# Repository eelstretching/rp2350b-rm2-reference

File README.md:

# RP2350B + RM2

Raspberry Pi's RP2350B minimal design (RPI-RP2350B-MINIMAL R4-S1, KiCad 10) with these additions:

- the **RM2** Wi-Fi/Bluetooth module (CYW43439) on **GPIO 43-46**
- the **8 MB APS6404L PSRAM** fitted on the second QSPI chip select, moved from GPIO0 to **GPIO47**
- **single-row headers**: J2/J3 are 1x29 / 1x28 rows with the GPIOs in order and **3V3 and GND
  pins at both ends**, in place of Pi's 2x26 headers with an all-GND outer row. That makes the
  board easy to use on perfboard, with 3.3 V on hand for level shifters and the like
- a **5 V input (VSYS) on J3 pin 2**, so the board can run without USB. As on a Pico, USB comes in
  through a Schottky diode (D2), so 5 V on the header can't back-feed a computer's USB port

That leaves **GPIO 0-42 free and in order** on the J2/J3 headers, instead of the Pico 2 W's gap
at 23/24/25/29.

Status: **schematic and layout done, DRC clean, not yet fabricated.** See "Layout" for what changed
on Pi's board.

## Pin map

| GPIO | Use |
|---|---|
| 0-42 | free, on J2/J3 (0/1 = default UART0) |
| 43 | RM2 WL_ON + BT_ON |
| 44 | RM2 gSPI CS |
| 45 | RM2 gSPI DATA: DI direct, DO through 470R (R14), IRQ through 10k (R15) |
| 46 | RM2 gSPI CLK |
| 47 | PSRAM chip select (XIP_SS_N[1]), 10k pull-up R13, 0R link R11 |

GPIO 43-47 aren't on the headers: they belong to the radio and the PSRAM.

The headers, from the USB end down:

| Header | Top | Middle | Bottom |
|---|---|---|---|
| J2 (left, 29 pins) | 3V3 | GP0-GP24 | GND, 3V3, GND |
| J3 (right, 28 pins) | 3V3, VSYS, GND, GND, GND | GP42-GP28, RUN, SWD, SWCLK, GP27-GP25 | 3V3, GND |

The radio circuit is the Pico 2 W's (and the RM2 datasheet's) on different pins:

- VIN and VDDIO go to +3V3, with 10u + 2x 100n local decoupling.
- WL_GPIO0 drives a green LED (D1) through 1k. That's the SDK's `CYW43_WL_GPIO_LED_PIN`.
- WL_GPIO1, WL_GPIO2 and the NC pins aren't connected.

The cyw43 driver takes any pins from the board header, so nothing else changes in firmware. On the
RP2350B a PIO block reaches either GPIO 0-31 or 16-47. The radio's PIO therefore sits in the
16-47 window, which means LED output PIOs for GPIO 0-15 must use a different PIO block.

## Power

The board runs from USB, or from 5 V on **J3 pin 2 (VSYS)**, which works like a Pico's VSYS pin.

- VSYS feeds U2, the 3.3 V regulator (NCP1117, linear). USB's VBUS reaches VSYS through D2
  (B5819W Schottky). D2 blocks 5 V on the header from flowing back into a computer, so you can leave
  USB plugged in for flashing and serial while the header powers the board. With both connected,
  the header supply (no diode drop) carries the load.
- Give VSYS 4.75-5.5 V. U2 needs about 1.2 V of headroom, and anything above 3.3 V plus that
  headroom turns into heat in U2.
- **From a 12 V supply** (the lights' supply, say), step it down to 5 V with a small buck module
  and wire that to VSYS and GND. Don't put 12 V on VSYS directly: U2 would burn (12 - 3.3) V times
  the board's current, nearly 1 W at 100 mA, which is too much for a SOT-223 on this copper.
- On USB alone, D2 drops about 0.3-0.4 V, which leaves U2 enough headroom from a normal USB port.
- The 3V3 pins are U2's output. They're fine for level shifters and sensors (tens of mA). U2 also
  carries the RP2350 and the radio, and it turns (VSYS - 3.3 V) times the total current into heat.
- VSYS has no reverse-polarity protection, so check the polarity before powering up.

## Using it on perfboard

J2 and J3 are single rows on the 0.1" grid, 1.7" (17 holes) apart, so the module drops straight
into perfboard, and every pin has free holes beside it.

- **Socket it and wire on the underside.** Put female headers on the perfboard and plug the module
  in, then wire underneath with thin insulated wire (Kynar or wire-wrap). The area under the module
  is free routing space. Socketing also gives the parts on the module's underside room: U4 (the
  PSRAM, 1.75 mm tall SOIC), R11, R13 and C22. Plain header pins pushed fully home leave only
  about 2.5 mm.
- **Keep the antenna end clear.** Let the RM2 end overhang the perfboard edge, or keep that area
  free of wires, copper and ground. Anything conductive close under the antenna detunes it.

Two traps:

- **Stripboard (Veroboard):** run the strips outward, perpendicular to the headers, so each pin
  gets its own strip. Then cut every strip somewhere between the two headers. Otherwise a strip
  runs under the module and joins each J2 pin to the J3 pin in the same row: GPIO0 to 3V3,
  GPIO1 to GND, and at the bottom 3V3 straight to GND.
- **Solderless breadboard:** the 1.7" span between the rows is too wide to straddle a standard
  breadboard.

## PSRAM in your own code

With pico-sdk 2.3.0 or later, linking `hardware_psram` brings the PSRAM up at boot. It reads
`PICO_PSRAM_CS_PIN` and `PICO_PSRAM_SIZE_BYTES`, which the board header already sets. The PSRAM then
appears as ordinary memory at 0x11000000.

- **Static data:** `__uninitialized_psram("name")` (or `__in_psram("name")` for initialised data)
  places a variable or array in PSRAM.
- **Dynamic allocation:** `firmware/psram_alloc` adds `psram_malloc`, `psram_calloc`,
  `psram_realloc`, `psram_memalign` and `psram_free`, plus `psram_heap_stats()`. These work like
  malloc (8-byte aligned, safe from both cores, not from interrupt handlers) but allocate from the
  PSRAM left after any PSRAM variables. The SDK's own `malloc` stays in the faster on-chip SRAM.
  It's a TLSF allocator with its control block in SRAM. To use it:

  ```cmake
  add_subdirectory(path/to/firmware/psram_alloc psram_alloc)
  target_link_libraries(my_app psram_alloc)
  ```

PSRAM is slower than SRAM, so use it for big, mostly-streamed data (frame and pixel buffers, audio,
network buffers). Keep stacks and hot data in SRAM. `firmware/psram_test` prints the throughput, and
is the first thing to run on a new board to check U4.

## Files

| Path | What |
|---|---|
| `RP2350B-RM2.kicad_sch` | schematic (single sheet, A3) |
| `RP2350B-RM2.kicad_pcb` | Pi's R4 layout, 18 mm longer, plus the RM2 and the PSRAM (see "Layout") |
| `rp2350b_rm2.kicad_sym`, `rp2350b_rm2.pretty/RPi_RM2.kicad_mod` | RM2 symbol and footprint (project libraries, already in `sym-lib-table` / `fp-lib-table`) |
| `bom-jlcpcb.csv` | BOM with LCSC numbers |
| `firmware/boards/rp2350b_rm2.h` | pico-sdk board header (CYW43 pins, 16 MB flash, 8 MB PSRAM on GPIO47) |
| `firmware/blink/` | bring-up test: blinks D1 through the radio, so it proves the RM2 is alive |
| `firmware/psram_test/` | bring-up test for the PSRAM: tests all 8 MB, measures throughput, exercises the heap |
| `firmware/psram_alloc/` | `psram_malloc()` / `psram_free()`: a heap in PSRAM for your own projects (TLSF, vendored) |
| `tools/kisch.py`, `tools/kirender.py` | netlist dump/check and rough PNG preview of a schematic, no KiCad needed |
| `tools/rm2_footprint.py` | generator for the RM2 footprint |
| `tools/update_pcb_from_sch.py`, `tools/layout_rm2.py` | the scripted Update PCB from Schematic and RM2/PSRAM layout pass that produced the board (run once, in KiCad's Python; kept for reference) |
| `docs/schematic-*.png` | rough schematic previews (full sheet, radio, PSRAM) |
| `docs/pcb-front.png`, `docs/pcb-back.png` | board renders (front copper and silk; back copper, mirrored) |

## BOM / JLCPCB

Every part has an LCSC number except these three:

- **U5 RM2**: not stocked at LCSC. Buy Raspberry Pi SC1169 (Pimoroni, The Pi Hut, Mouser) and
  hand-solder it. The footprint's pads run 0.5 mm past the module edge to make that easier.
- **SW1/SW2** (Wurth 434133025816): not at LCSC. Use JLC global sourcing or hand-solder, or swap
  in an LCSC tact switch and change the footprint.
- **J2/J3** 1x29 and 1x28 2.54 mm headers: through-hole, hand-solder (or socket, see "Using it on
  perfboard").

Passives were swapped from Pi's Murata/Yageo parts to JLC basic equivalents with the same value,
size and dielectric. The 100n parts are 16 V instead of 25 V, which is fine on 3.3 V.

## Layout

The board is Pi's R4 layout with **Update PCB from Schematic** applied, and the areas below added
or changed. Every Pi footprint stays where it was apart from the bottom mounting holes (MH3, MH4)
and the headers (J2, J3), which are now single rows on Pi's signal columns. Pi's JST debug
connector (J4) is gone, since SWD and SWCLK are on J3. D2 is new, next to the USB connector. Pi's
tracks are untouched apart from the U4 fan-out, the R11 stub, the last stretch of GPIO43-47's runs
to J3, and SWD/SWCLK where they used to pass through J4. Pi's VBUS pour is split in two around D2.

**RM2 end.** The board is 18 mm longer (89.5 x 52 mm), and the extra length is at the end away from
USB, as on the Pico 2 W. The headers stay on both long edges. The RM2 (U5) sits between them,
centred, with its antenna end (pins 1 and 21) at the new bottom edge. The module's top edge clears
Pi's "Minimal Design Example R4" silkscreen line.

- Antenna: a rule area across the full board width, from the module's antenna line to the bottom
  edge, blocks copper, tracks and vias on both layers. That covers the footprint's own keep-out plus
  the copper on either side of it.
- Ground: there's a solid back-layer GND pour under the module and a top-layer GND pour under the
  module body. Each of the six RM2 GND pads (1, 4, 7, 11, 15, 21) has its own via to the back plane,
  within 2.4 mm of the pad centre.
- gSPI: GPIO43-46 run on top copper the whole way. Pi's runs to J3's top pins (now 3V3 and GND)
  stop just short of them and slip between those pins into four lanes beside J3, where Pi's outer
  GND column used to be, 0.7 mm apart. Below J3 they turn in toward the module. SCLK, DI and DO
  land on the module's right side, and CS and WL_ON wrap over its top.
- Length: the cost of the long-board layout is length. Each gSPI net runs 118-124 mm from U1
  (Pico 2 W: a few cm), about 30 mm of which is Pi's existing U1-to-J3 routing. That's still short
  next to a clock period at cyw43's default gSPI rate. But it's around the length where fast GPIO
  edges start to ring, and SCLK has no series resistor. If the radio misbehaves at bring-up, slow
  the bus with a higher `CYW43_PIO_CLOCK_DIV_INT` before suspecting anything else.
- R14 (DO, 470R) sits 1 mm from the DO pad, and R15 (IRQ, 10k) sits next to it on GPIO45. The IRQ
  line (host wake) takes the back layer for 12 mm to get from R15 to its pad under CS. It's the
  only radio signal off the top layer.
- Power: VIN has C24 (100n) and C23 (10u) next to it, and VDDIO has C25 (100n). Both sit in the
  top-layer +3V3 pour, which joins Pi's pour above the module. A sheet-resistance estimate of that
  copper puts U2's output to the RM2's VIN at about 15 mOhm, roughly 5 mV at a 300 mA transmit
  peak.
- D1 (WL_GPIO0 LED) and R16 sit just above the module's top-right corner.

The gSPI lanes run alongside J3's pins, so expect a little crosstalk from SCLK onto anything wired
to J3.

**Mounting holes.** MH3 and MH4 move from Pi's old bottom edge to the new end of the board, at the
same x as the top pair (86.03 and 113.97 mm) and 4 mm from the edge, again like the top pair. The
four holes keep Pi's rectangular pattern, now 27.94 x 81.5 mm. The top pair can't move into the
true corners because J2/J3 pin 1 is there. At the bottom, the holes flank the RM2's antenna
about 5 mm from its ends, as on the Pico 2 W. The antenna rule area allows them because they're
NPTH holes with no copper.

**Headers.** J2/J3 swap Pi's 2x26 Samtec headers for stock 1x29 / 1x28 2.54 mm headers on Pi's
inner (signal) columns, so every GPIO keeps its pad and Pi's routing to it. The outer GND column is
gone, and the top-layer +3V3 pour and the back GND plane fill its place.
- GND pins connect to the back plane.
- J3's top 3V3 pin joins the pour above J3, which U2's pin 2 feeds directly, about 3 mOhm from
  U2's output.
- J3 pin 2 is VSYS (see "VSYS on J3" below).
- J3's bottom 3V3 pin sits between GPIO25's pin and the WL_ON lane, so it gets a track into the
  pour and a solid (not thermal) connection.
- J2's 3V3 pins take the pour around them, 9-17 mOhm from U2.

Pi's silkscreen labels for J3's top five pins now read 3V3, VSYS and GND, "ADC 40-47" reads "ADC 40-42",
and the "Outer Row GND" notes are gone. The new bottom pins get labels in the same style.

**VSYS on J3.** D2 (SOD-123) sits between the USB connector, C1 and U2, in what was Pi's VBUS
pour. That pour is split in two. A small USB-side piece runs from J1's VBUS pin to D2's anode, and
the rest is VSYS: D2's cathode, C1 and U2's input. A 0.6 mm VSYS track runs from D2's cathode
straight through U2's input pad, under U2 between its pins and its tab, and diagonally up to J3
pin 2. Going under U2 rather than past C1 keeps the 3V3 pour above it (around the top mounting
hole and J3 pin 1) joined to U2's pin 2. The back GND plane is unbroken under the whole route.

**U4 (PSRAM).** U4 swaps to `Package_SO:SOIC-8_3.9x4.9mm_P1.27mm` at Pi's spot on the back, under
U3. Pi's back-side fan-out vias for the second flash sat where the 150 mil pads now are. They are
replaced by five new vias between the pad rows: SD1/SD2 cross on top and drop beside U4's right
column, SD3/SCLK cross on top between those vias and drop beside the left column, and SD0 drops from
U3's SD0 run and passes under U4 on the back. Pi's FLASH2_SS run from R11/R13 now carries PSRAM_CS.

**J4 (debug connector) removed.** SWD and SWCLK come out on J3 (pins 22 and 23, next to RUN on
pin 21), so Pi's JST debug connector is gone, along with its BOM line, its GND stubs and vias, and
the "DEBUG" silkscreen. Pi ran SWD and SWCLK through J4's pads on their way to J3. They now carry on
straight along the same 45-degree lines into their existing runs to J3.

**PSRAM CS on GPIO47.** R11's old GPIO0 stub is gone. GPIO47 now reaches R11 through a via on Pi's
GPIO47 run, which stops there instead of going on to J3, and a back-layer track. GPIO0's own route
to J2 is unchanged.

## Verification so far

- `python3 tools/kisch.py RP2350B-RM2.kicad_sch` reports no dangling pins and no multi-named nets.
  A net-by-net diff against Pi's original shows only the intended changes (RM2 nets, PSRAM CS
  GPIO0 to GPIO47, new decoupling).
- The RM2 pad positions match SparkFun's independently drawn RM2 footprint (XRP Controller) at
  every pad's inner edge.
- `firmware/blink` compiles against pico-sdk 2.3.0 with this board header.
- `firmware/psram_test` builds against pico-sdk 2.3.0 (arm-none-eabi-gcc 13.2), with no warnings
  from its own code under `-Wall -Wextra -Wshadow -Wconversion`. Its heap code (psram_alloc and the
  heap part of the test) passes on a host build in 32-bit mode, so TLSF's alignment behaves as on
  the RP2350, including under AddressSanitizer and UBSan. Not yet run on hardware.
- Checked headless with KiCad 10.0.6 (`kicad-cli` and pcbnew's Python), using the stock global
  library tables:
  - `kicad-cli pcb drc --schematic-parity --severity-all` reports 0 unconnected items and 0
    schematic-parity issues. The only remaining violations are 45 notes that the footprint library
    `RPI_COMPILED` isn't in the library table. Pi's original board has the same notes, because its
    footprints are embedded in the board.
  - `kicad-cli sch erc` reports 4 real items, in parts of the schematic this layout didn't touch: U2's
    two OUT pins tied together, U1 VREG_AVDD and #PWR16 "not driven" (power-flag nits), and one
    off-grid wire end. Everything else is the same library-table notes for Pi's libraries.
- Not yet opened in the KiCad GUI. After loading, refill zones (B) before plotting.

## License

Raspberry Pi's design is MIT (see `LICENSE-RaspberryPi.txt`); the additions here are MIT too.
The board header is BSD-3-Clause, derived from pico-sdk board headers.

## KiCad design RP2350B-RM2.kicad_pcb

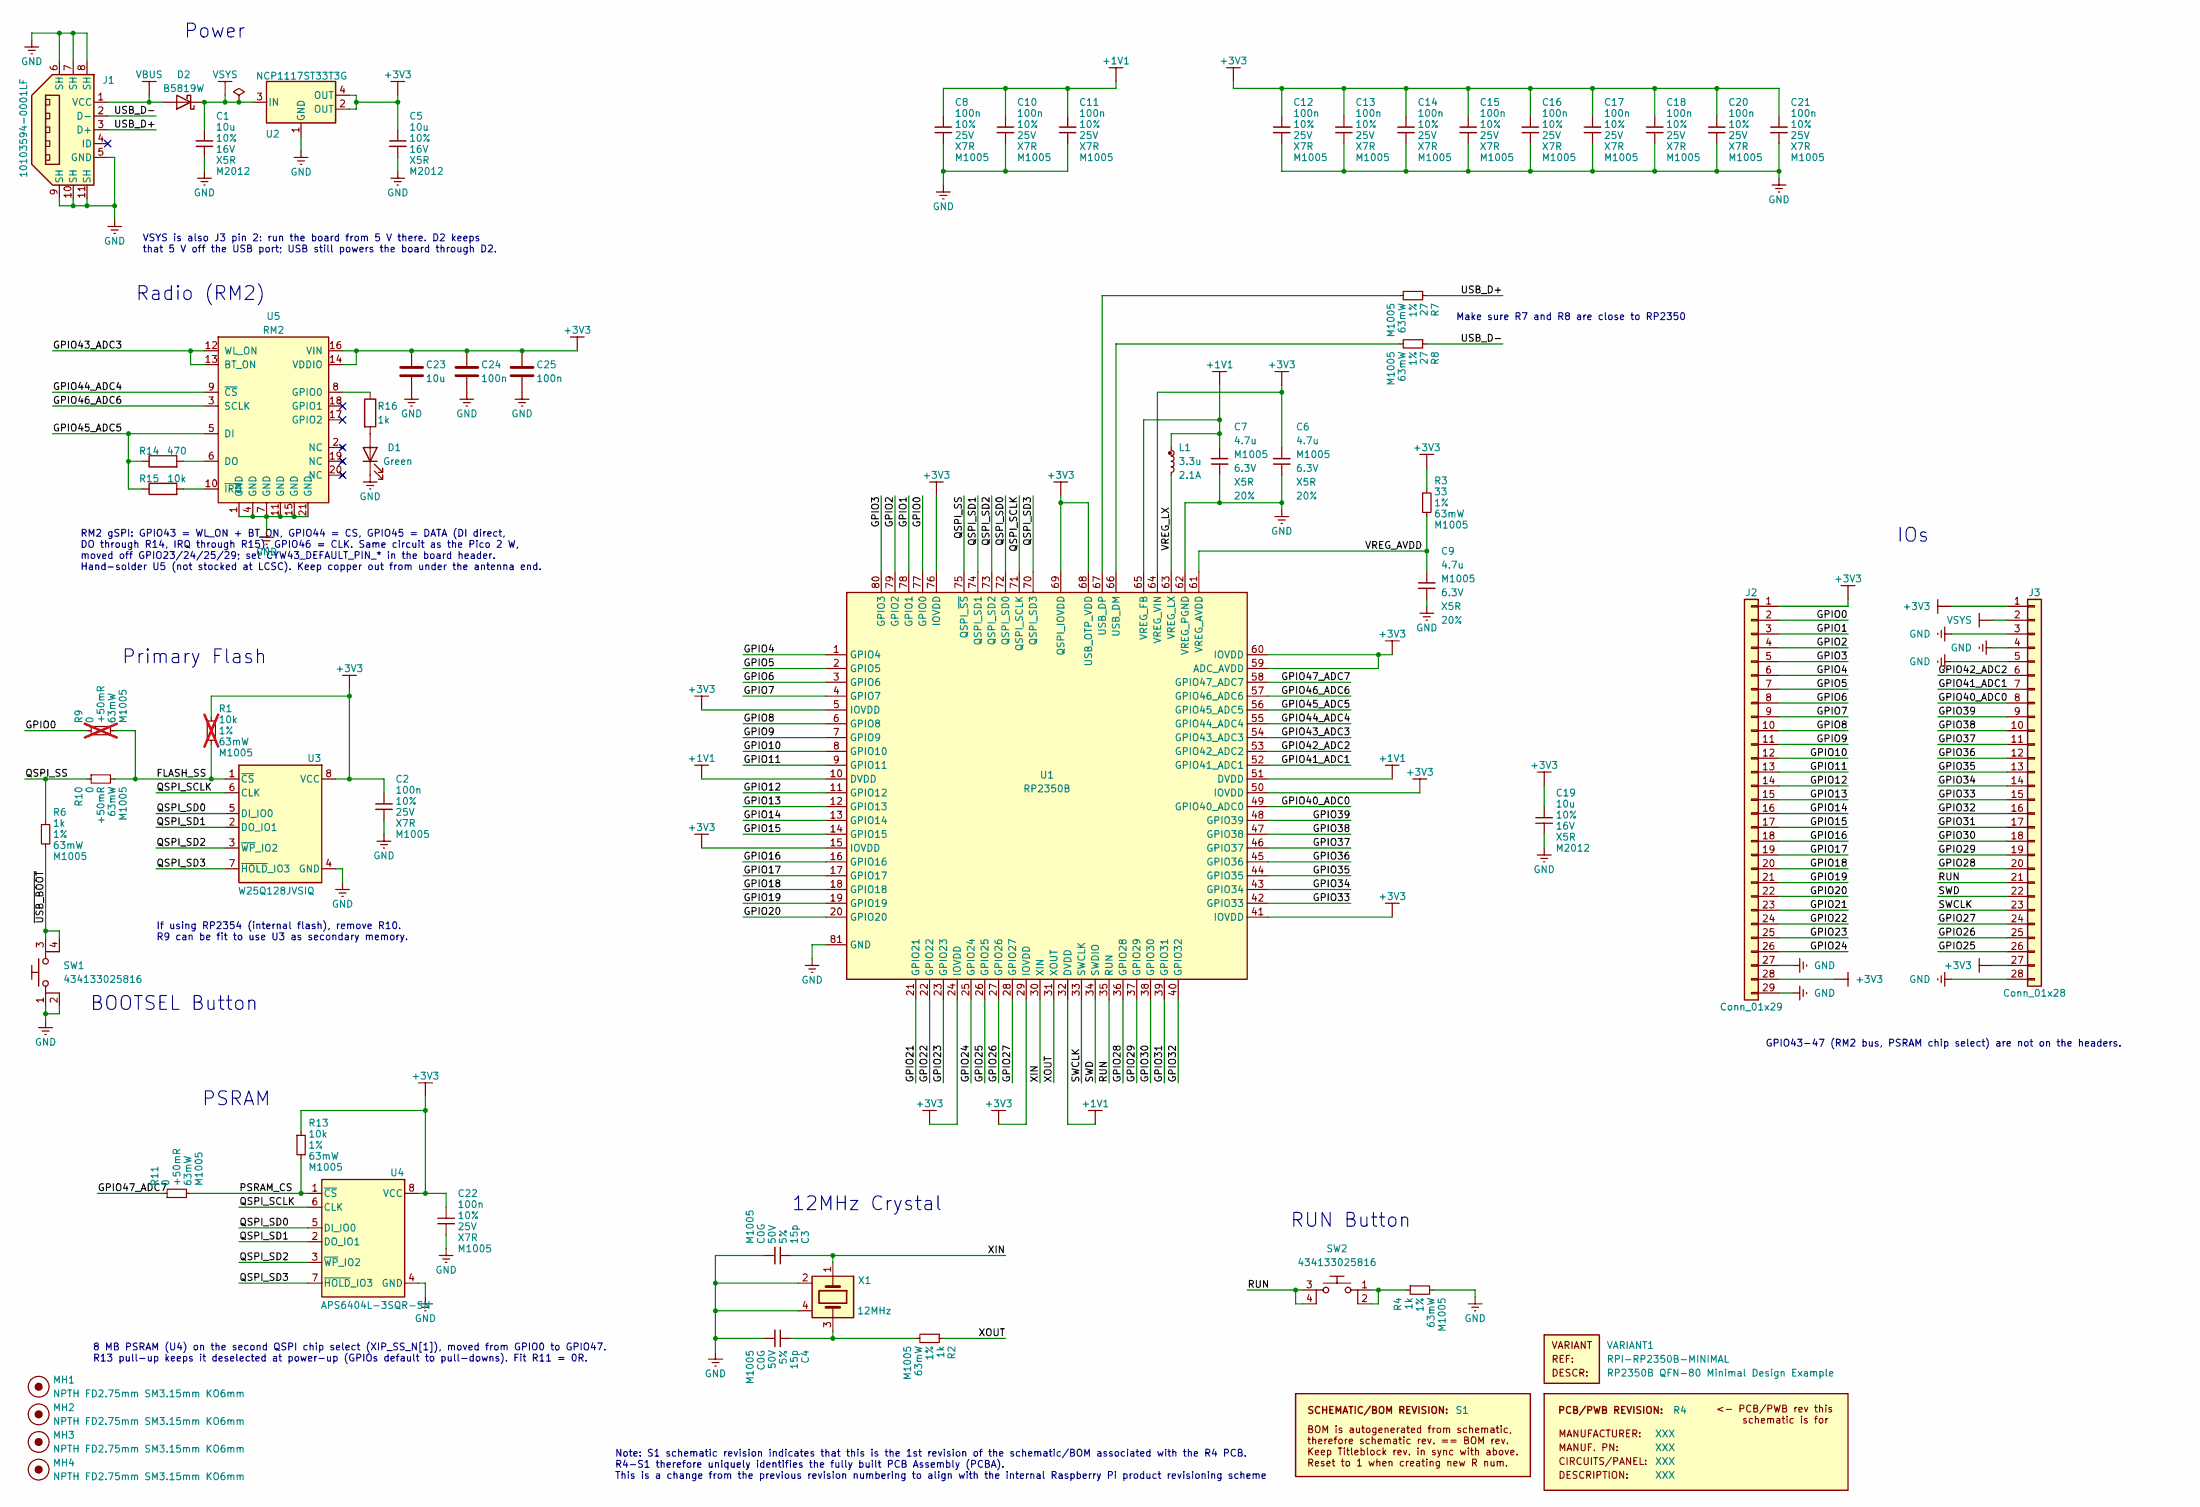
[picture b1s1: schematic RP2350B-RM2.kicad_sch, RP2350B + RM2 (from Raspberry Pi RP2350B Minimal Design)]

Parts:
C1, C5, C19: 10u; generic_capc2012x125; voltage 16V; tolerance 10%; part_uid RP-01GYSK-AVBE41; LCSC C15850
C2, C8, C10, C11, C12, C13, C14, C15, C16, C17, C18, C20, C21, C22: 100n; generic_capc1005x50; voltage 25V; tolerance 10%; part_uid RP-01BJ9Y-KRGF41; LCSC C1525
C3, C4: 15p; generic_capc1005x50; voltage 50V; tolerance 5%; part_uid RP-01C89W-LLY9XV; LCSC C1548
C6, C7: 4.7u; generic_capc1005x50_wide; voltage 6.3V; tolerance 20%; part_uid RP-019A1P-0C2GHY; LCSC C23733
C9: 4.7u; generic_capc1005x50; voltage 6.3V; tolerance 20%; part_uid RP-019A1P-0C2GHY; LCSC C23733
C23: 10u; C_0805_2012Metric; manufacturer_pn CL21A106KAYNNNE; LCSC C15850
C24, C25: 100n; C_0402_1005Metric; manufacturer_pn CL05B104KO5NNNC; LCSC C1525
D1: Green; LED_0603_1608Metric; manufacturer_pn 19-217/GHC-YR1S2/3T; LCSC C72043
D2: B5819W; D_SOD-123; manufacturer_pn B5819W SL; LCSC C8598
J1: 10103594-0001LF; amphenol_10103594-0001lf; part_uid RP-019A1P-1JAX7V; LCSC C428495
J2: Conn_01x29; PinHeader_1x29_P2.54mm_Vertical; manufacturer_pn 1x29 2.54 mm pin header
J3: Conn_01x28; PinHeader_1x28_P2.54mm_Vertical; manufacturer_pn 1x28 2.54 mm pin header
L1: 3.3u; abracon_aota-b201610s3r3-101-t; tolerance 20%; part_uid RP-01GY5D-2VC7WP; LCSC C42411119
MH1, MH2, MH3, MH4: NPTH FD2.75mm SM3.15mm KO6mm; none_mh_npth_fd2p75mm_sm3p15mm_ko6mm; part_uid RP-01HF5R-LCTEJS
PCB1: R4; manufacturer_pn XXX
R1: 10k; generic_resc1005x35; tolerance 1%; voltage 50V; part_uid RP-019A1P-53DHSX; LCSC C25744; not fitted
R2, R4, R6: 1k; generic_resc1005x35; tolerance 1%; voltage 50V; part_uid RP-019A1P-4Z6ZWY; LCSC C11702
R3: 33; generic_resc1005x35; tolerance 1%; voltage 50V; part_uid RP-019A1P-58PW9L; LCSC C25105
R7, R8: 27; generic_resc1005x35; tolerance 1%; voltage 50V; part_uid RP-01C89V-LTEYC4; LCSC C25100
R9: 0; generic_resc1005x35; tolerance +50mR; voltage 50V; part_uid RP-019A1P-4Y4V63; LCSC C17168; not fitted
R10, R11: 0; generic_resc1005x35; tolerance +50mR; voltage 50V; part_uid RP-019A1P-4Y4V63; LCSC C17168
R13: 10k; generic_resc1005x35; tolerance 1%; voltage 50V; part_uid RP-019A1P-53DHSX; LCSC C25744
R14: 470; R_0402_1005Metric; manufacturer_pn 0402WGF4700TCE; LCSC C25117
R15: 10k; R_0402_1005Metric; manufacturer_pn 0402WGF1002TCE; LCSC C25744
R16: 1k; R_0402_1005Metric; manufacturer_pn 0402WGF1001TCE; LCSC C11702
SBREV1: S1
SW1, SW2: 434133025816; wurthelek_434133025816; part_uid RP-01H0MT-6E9H8F
U1: RP2350B; rpi_rp2350b_vias; part_uid RP-01HA9H-ABBLJN; LCSC C42415655
U2: NCP1117ST33T3G; onsemi_ncp1117st33t3g; voltage 3.3V; part_uid RP-01JWD9-7JRX6J; LCSC C26537
U3: W25Q128JVSIQ; generic_soic127p790x195-8; voltage 2.7-3.6V; part_uid RP-01JWD4-F1H4N9; LCSC C97521
U4: APS6404L-3SQR-SN; SOIC-8_3.9x4.9mm_P1.27mm; voltage 2.7-3.6V; manufacturer_pn APS6404L-3SQR-SN; LCSC C5333729
U5: RM2; RPi_RM2; manufacturer_pn SC1169 (RMC20452T)
VARIANT1: RPI-RP2350B-MINIMAL
X1: 12MHz; generic_xtalcc320x250x80-4; tolerance 30ppm; part_uid RP-01G8X7-GS352B; LCSC C20625731

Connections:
+1V1: C7.1, C8.1, C10.1, C11.1, L1.1, U1.10 (DVDD), U1.32 (DVDD), U1.51 (DVDD), U1.65 (VREG_FB)
+3V3: C2.1, C5.1, C6.1, C12.1, C13.1, C14.1, C15.1, C16.1, C17.1, C18.1, C19.1, C20.1, C21.1, C22.1, C23.1, C24.1, C25.1, J2.1, J2.28, J3.1, J3.27, R1.1, R3.1, R13.1, U1.5 (IOVDD), U1.15 (IOVDD), U1.24 (IOVDD), U1.29 (IOVDD), U1.41 (IOVDD), U1.50 (IOVDD), U1.59 (ADC_AVDD), U1.60 (IOVDD), U1.64 (VREG_VIN), U1.68 (USB_OTP_VDD), U1.69 (QSPI_IOVDD), U1.76 (IOVDD), U2.2 (OUT), U2.4 (OUT), U3.8 (VCC), U4.8 (VCC), U5.14 (VDDIO), U5.16 (VIN)
/FLASH_SS: R1.2, R9.2, R10.2, U3.1 (~CS)
/GPIO0: J2.2, R9.1, U1.77 (GPIO0)
/GPIO1: J2.3, U1.78 (GPIO1)
/GPIO2: J2.4, U1.79 (GPIO2)
/GPIO3: J2.5, U1.80 (GPIO3)
/GPIO4: J2.6, U1.1 (GPIO4)
/GPIO5: J2.7, U1.2 (GPIO5)
/GPIO6: J2.8, U1.3 (GPIO6)
/GPIO7: J2.9, U1.4 (GPIO7)
/GPIO8: J2.10, U1.6 (GPIO8)
/GPIO9: J2.11, U1.7 (GPIO9)
/GPIO10: J2.12, U1.8 (GPIO10)
/GPIO11: J2.13, U1.9 (GPIO11)
/GPIO12: J2.14, U1.11 (GPIO12)
/GPIO13: J2.15, U1.12 (GPIO13)
/GPIO14: J2.16, U1.13 (GPIO14)
/GPIO15: J2.17, U1.14 (GPIO15)
/GPIO16: J2.18, U1.16 (GPIO16)
/GPIO17: J2.19, U1.17 (GPIO17)
/GPIO18: J2.20, U1.18 (GPIO18)
/GPIO19: J2.21, U1.19 (GPIO19)
/GPIO20: J2.22, U1.20 (GPIO20)
/GPIO21: J2.23, U1.21 (GPIO21)
/GPIO22: J2.24, U1.22 (GPIO22)
/GPIO23: J2.25, U1.23 (GPIO23)
/GPIO24: J2.26, U1.25 (GPIO24)
/GPIO25: J3.26, U1.26 (GPIO25)
/GPIO26: J3.25, U1.27 (GPIO26)
/GPIO27: J3.24, U1.28 (GPIO27)
/GPIO28: J3.20, U1.36 (GPIO28)
/GPIO29: J3.19, U1.37 (GPIO29)
/GPIO30: J3.18, U1.38 (GPIO30)
/GPIO31: J3.17, U1.39 (GPIO31)
/GPIO32: J3.16, U1.40 (GPIO32)
/GPIO33: J3.15, U1.42 (GPIO33)
/GPIO34: J3.14, U1.43 (GPIO34)
/GPIO35: J3.13, U1.44 (GPIO35)
/GPIO36: J3.12, U1.45 (GPIO36)
/GPIO37: J3.11, U1.46 (GPIO37)
/GPIO38: J3.10, U1.47 (GPIO38)
/GPIO39: J3.9, U1.48 (GPIO39)
/GPIO40_ADC0: J3.8, U1.49 (GPIO40_ADC0)
/GPIO41_ADC1: J3.7, U1.52 (GPIO41_ADC1)
/GPIO42_ADC2: J3.6, U1.53 (GPIO42_ADC2)
/GPIO43_ADC3: U1.54 (GPIO43_ADC3), U5.12 (WL_ON), U5.13 (BT_ON)
/GPIO44_ADC4: U1.55 (GPIO44_ADC4), U5.9 (~CS)
/GPIO45_ADC5: R14.1, R15.1, U1.56 (GPIO45_ADC5), U5.5 (DI)
/GPIO46_ADC6: U1.57 (GPIO46_ADC6), U5.3 (SCLK)
/GPIO47_ADC7: R11.1, U1.58 (GPIO47_ADC7)
/PSRAM_CS: R11.2, R13.2, U4.1 (~CS)
/QSPI_SCLK: U1.71 (QSPI_SCLK), U3.6 (CLK), U4.6 (CLK)
/QSPI_SD0: U1.72 (QSPI_SD0), U3.5 (DI_IO0), U4.5 (DI_IO0)
/QSPI_SD1: U1.74 (QSPI_SD1), U3.2 (DO_IO1), U4.2 (DO_IO1)
/QSPI_SD2: U1.73 (QSPI_SD2), U3.3 (~WP_IO2), U4.3 (~WP_IO2)
/QSPI_SD3: U1.70 (QSPI_SD3), U3.7 (~HOLD_IO3), U4.7 (~HOLD_IO3)
/QSPI_SS: R6.1, R10.1, U1.75 (QSPI_~SS)
/RUN: J3.21, SW2.3, SW2.4, U1.35 (RUN)
/SWCLK: J3.23, U1.33 (SWCLK)
/SWD: J3.22, U1.34 (SWDIO)
/USB_D+: J1.3 (D+), R7.1
/USB_D-: J1.2 (D-), R8.1
/VREG_AVDD: C9.1, R3.2, U1.61 (VREG_AVDD)
/VREG_LX: L1.2, U1.63 (VREG_LX)
/XIN: C3.1, U1.30 (XIN), X1.1
/XOUT: R2.1, U1.31 (XOUT)
/~USB_BOOT: R6.2, SW1.3, SW1.4
GND: C1.2, C2.2, C3.2, C4.2, C5.2, C6.2, C7.2, C8.2, C9.2, C10.2, C11.2, C12.2, C13.2, C14.2, C15.2, C16.2, C17.2, C18.2, C19.2, C20.2, C21.2, C22.2, C23.2, C24.2, C25.2, D1.1 (K), J1.5 (GND), J1.6 (SH), J1.7 (SH), J1.8 (SH), J1.9 (SH), J1.10 (SH), J1.11 (SH), J2.27, J2.29, J3.3, J3.4, J3.5, J3.28, R4.2, SW1.1, SW1.2, U1.62 (VREG_PGND), U1.81 (GND), U2.1 (GND), U3.4 (GND), U4.4 (GND), U5.1 (GND), U5.4 (GND), U5.7 (GND), U5.11 (GND), U5.15 (GND), U5.21 (GND), X1.2, X1.4
unnamed: C4.1, R2.2, X1.3
unnamed: D1.2 (A), R16.2
unnamed: R4.1, SW2.1, SW2.2
unnamed: R8.2, U1.66 (USB_DM)
unnamed: R7.2, U1.67 (USB_DP)
unnamed: R14.2, U5.6 (DO)
unnamed: R16.1, U5.8 (GPIO0)
unnamed: R15.2, U5.10 (~IRQ)
VBUS: D2.2 (A), J1.1 (VCC)
VSYS: C1.1, D2.1 (K), J3.2, U2.3 (IN)

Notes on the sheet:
8 MB PSRAM (U4) on the second QSPI chip select (XIP_SS_N[1]), moved from GPIO0 to GPIO47. R13 pull-up keeps it deselected at power-up (GPIOs default to pull-downs). Fit R11 = 0R.
IOs
If using RP2354 (internal flash), remove R10. R9 can be fit to use U3 as secondary memory.
GPIO43-47 (RM2 bus, PSRAM chip select) are not on the headers.
Note: S1 schematic revision indicates that this is the 1st revision of the schematic/BOM associated with the R4 PCB. R4-S1 therefore uniquely identifies the fully built PCB Assembly (PCBA). This is a change from the previous revision numbering to align with the internal Raspberry Pi product revisio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
Radio (RM2)
RUN Button
RM2 gSPI: GPIO43 = WL_ON + BT_ON, GPIO44 = CS, GPIO45 = DATA (DI direct, DO through R14, IRQ through R15), GPIO46 = CLK. Same circuit as the Pico 2 W, moved off GPIO23/24/25/29; set CYW43_DEFAULT_PIN_* in the board header. Hand-solder U5 (not stocked at LCSC). Keep copper out from under the antenna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
Primary Flash
BOOTSEL Button
12MHz Crystal
Make sure R7 and R8 are close to RP2350
PSRAM
Power
VSYS is also J3 pin 2: run the board from 5 V there. D2 keeps that 5 V off the USB port; USB still powers the board through D2.

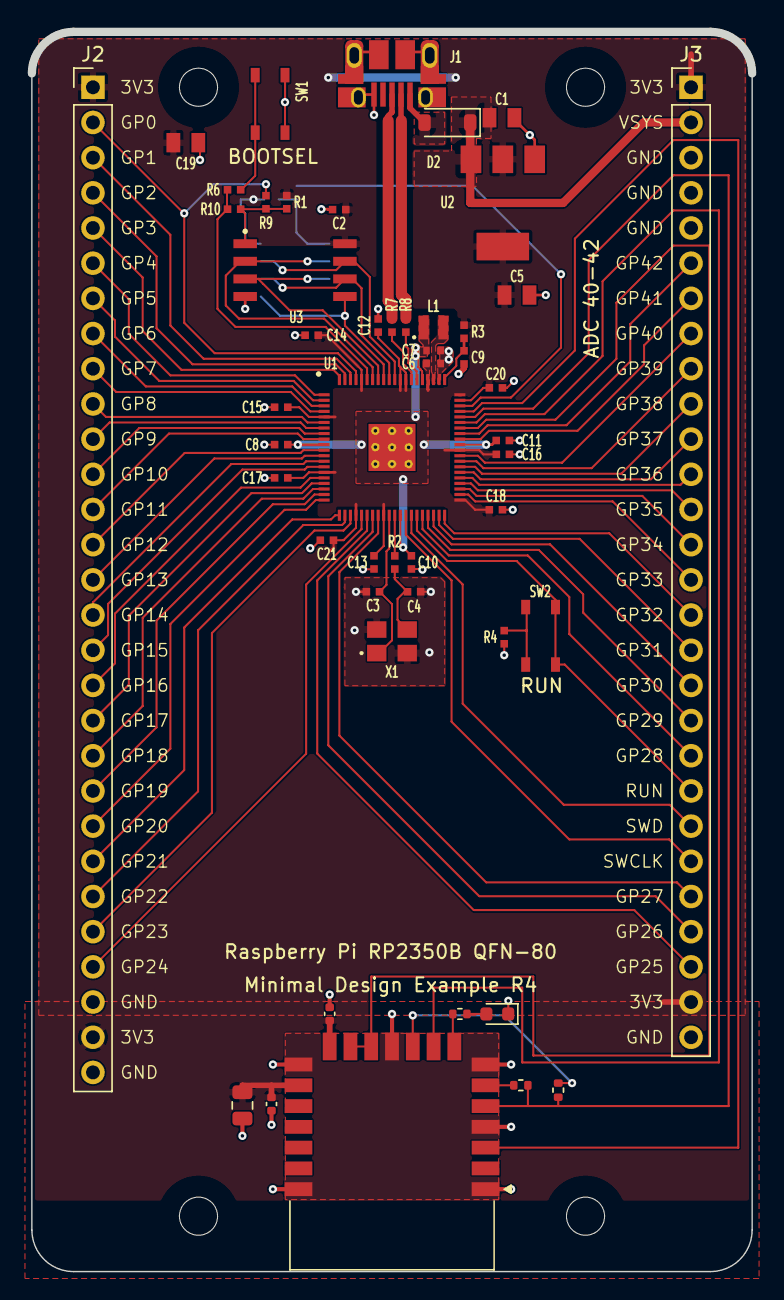
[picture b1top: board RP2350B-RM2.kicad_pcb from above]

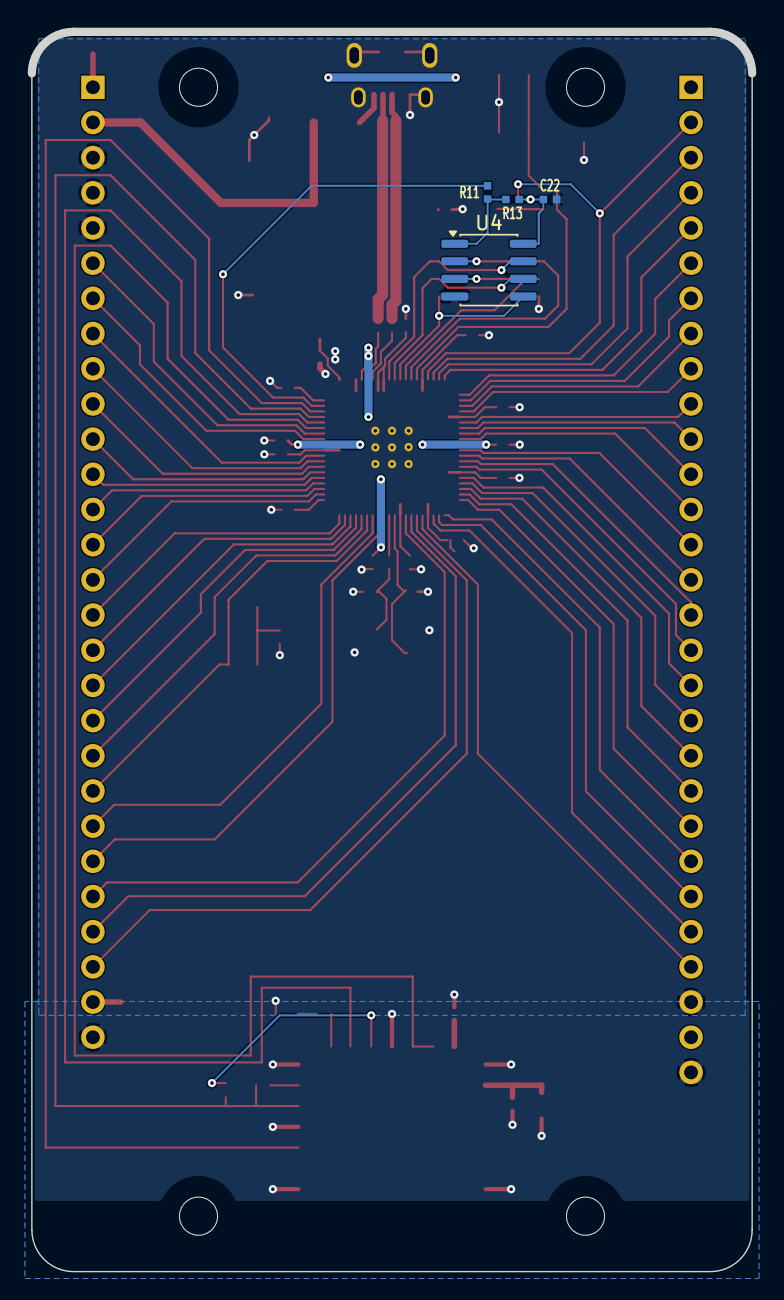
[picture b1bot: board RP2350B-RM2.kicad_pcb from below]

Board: 2 copper layers, 52.0 x 89.5 mm, 57 parts (4 on the bottom side), 79 nets.

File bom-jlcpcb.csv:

Comment,Designator,Footprint,LCSC,Manufacturer PN,Qty,Note
10u,"C1,C5,C19",generic_capc2012x125,C15850,CL21A106KAYNNNE,3,
100n,"C2,C8,C10,C11,C12,C13,C14,C15,C16,C17,C18,C20,C21,C22",generic_capc1005x50,C1525,CL05B104KO5NNNC,14,
15p,"C3,C4",generic_capc1005x50,C1548,0402CG150J500NT,2,
4.7u,"C6,C7",generic_capc1005x50_wide,C23733,CL05A475MP5NRNC,2,
4.7u,C9,generic_capc1005x50,C23733,CL05A475MP5NRNC,1,
10u,C23,C_0805_2012Metric,C15850,CL21A106KAYNNNE,1,
100n,"C24,C25",C_0402_1005Metric,C1525,CL05B104KO5NNNC,2,
Green,D1,LED_0603_1608Metric,C72043,19-217/GHC-YR1S2/3T,1,
B5819W,D2,D_SOD-123,C8598,B5819W SL,1,
10103594-0001LF,J1,amphenol_10103594-0001lf,C428495,10103594-0001LF,1,
Conn_01x29,J2,PinHeader_1x29_P2.54mm_Vertical,,1x29 2.54 mm pin header,1,Through-hole: hand-solder
Conn_01x28,J3,PinHeader_1x28_P2.54mm_Vertical,,1x28 2.54 mm pin header,1,Through-hole: hand-solder
3.3u,L1,abracon_aota-b201610s3r3-101-t,C42411119,AOTA-B201610S3R3-101-T,1,
1k,"R2,R4,R6",generic_resc1005x35,C11702,0402WGF1001TCE,3,
33,R3,generic_resc1005x35,C25105,0402WGF330JTCE,1,
27,"R7,R8",generic_resc1005x35,C25100,0402WGF270JTCE,2,
0,"R10,R11",generic_resc1005x35,C17168,0402WGF0000TCE,2,
10k,R13,generic_resc1005x35,C25744,0402WGF1002TCE,1,
470,R14,R_0402_1005Metric,C25117,0402WGF4700TCE,1,
10k,R15,R_0402_1005Metric,C25744,0402WGF1002TCE,1,
1k,R16,R_0402_1005Metric,C11702,0402WGF1001TCE,1,
434133025816,"SW1,SW2",wurthelek_434133025816,,434133025816,2,"Not at LCSC: JLC global sourcing, or hand-solder"
RP2350B,U1,rpi_rp2350b_vias,C42415655,RP2350B,1,
NCP1117ST33T3G,U2,onsemi_ncp1117st33t3g,C26537,NCP1117ST33T3G,1,
W25Q128JVSIQ,U3,generic_soic127p790x195-8,C97521,W25Q128JVSIQ,1,
APS6404L-3SQR-SN,U4,SOIC-8_3.9x4.9mm_P1.27mm,C5333729,APS6404L-3SQR-SN,1,
RM2,U5,RPi_RM2,,SC1169 (RMC20452T),1,Not at LCSC: buy RM2 (Raspberry Pi SC1169) and hand-solder
12MHz,X1,generic_xtalcc320x250x80-4,C20625731,ABM8-272-T3,1,

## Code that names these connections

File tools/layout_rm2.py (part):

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
- U4 is now a 150 mil SOIC-8 under U3, so the back-side fan-out vias that sat where
  its pads now are get replaced by a new fan-out between the pad rows.
- PSRAM chip select moved from GPIO0 to GPIO47, so R11's GPIO0 stub comes off and a
  GPIO47 run (back layer) goes in.
- GPIO43-47 no longer go to J3, so Pi's runs to those pins are cut short: the radio
  lines turn into lanes beside J3, and GPIO47 ends at the via to R11.
- The JST debug connector J4 is gone (SWD/SWCLK are on J3), so its GND stubs come off
  and SWD/SWCLK, which ran through its pads, run straight on to J3.
- J3 pin 2 is VSYS, the regulator input, and USB VBUS now reaches it through a Schottky
  (D2), so Pi's VBUS pour is split into a USB side and a VSYS side.

The board is stretched 18 mm at the end away from USB, like a Pico 2 W, and the RM2
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       for p in u5.Pads()}
assert pad['1'] == (106.75, 153.55) and pad['9'] == (103.0, 143.25) and pad['16'] == (93.25, 146.05), pad

G45, G46, G44, G43 = '/GPIO45_ADC5', '/GPIO46_ADC6', '/GPIO44_ADC4', '/GPIO43_ADC3'
# J3's top five pins (GPIO47-43 on Pi's board) are 3V3/GND now. Pi's diagonals to them stop
# short, slip between the J3 pins, and run down four lanes between J3 and the board edge,
# where the outer GND column used to be.
L_WL, L_CS, L_DI, L_SCK = 122.9, 123.6, 124.3, 125.0
for n, (x0, y0), gap_y in ((G46, (113.2, 84.93), 77.81), (G45, (114.2, 86.47), 80.35),
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via('Net-(U5-~{IRQ})', 101.5, 141.0)
track('Net-(U5-~{IRQ})', F, (101.5, 141.0), pad['10'])
# LED: pad 8 -> R16 -> D1 -> GND
track('Net-(U5-GPIO0)', F, (104.39, 140.9), (104.39, 143.25))
track('Net-(D1-A)', F, (105.41, 140.9), (106.81, 140.9))
track('GND', F, (108.39, 140.9), (108.4, 139.95))
via('GND', 108.4, 139.95)
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    via('GND', *v)

# J2/J3 are single-row headers on Pi's inner (signal) columns; the outer GND columns are gone.
# J2: 3V3, GPIO0-24, GND, 3V3, GND.  J3: 3V3, VSYS, GND x3, GPIO42-25 (RUN/SWD/SWCLK as before), 3V3, GND.
place('J2', 78.41, 74.0, 0)
place('J3', 121.59, 74.0, 0)
# J3's 3V3 pins: the top one joins the +3V3 pour above J3; the bottom one sits between Pi's GPIO25
# pin and the WL_ON lane, so it gets a track into the pour and a solid connection
track('+3V3', F, (121.59, 74.0), (121.59, 71.6), w=0.4)
track('+3V3', F, (121.59, 140.04), (119.6, 140.04), w=0.4)
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for y, text in ((140.04, '3V3'), (142.58, 'GND')):
    silk_label(text, 119.685, y, RIGHT)
# Pi's silkscreen: J3's top labels become the power pins, ADC now ends at 42, no outer row
relabel = {'GP47': '3V3', 'GP46': 'VSYS', 'GP45': 'GND', 'GP44': 'GND', 'GP43': 'GND'}
for d in list(B.GetDrawings()):
    if d.GetClass() != 'PCB_TEXT' or d.GetLayer() != pcbnew.F_SilkS:
        continue
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    if d.GetClass() == 'PCB_TEXT' and d.GetText() == 'DEBUG':
        B.Delete(d)

# ---------------------------------------------------------------- R11: GPIO0 -> GPIO47
remove_tracks('/GPIO0', BK, ((90.9, 81.0), (93.02, 81.0)), ((93.02, 81.0), (93.1, 81.08)))
# GPIO47 no longer goes to J3: Pi's run is cut back to a via that takes it to R11
remove_tracks('/GPIO47_ADC7', F, ((112.2, 83.39), (121.59, 74.0)), ((112.2, 92.791231), (112.2, 83.39)))
track('/GPIO47_ADC7', F, (112.2, 92.791231), (112.2, 87.5))
via('/GPIO47_ADC7', 112.2, 87.5)
track('/GPIO47_ADC7', BK, (112.2, 87.5), (105.815, 81.115), (93.1, 81.115))

ni = B.GetNetInfo().GetNetItem('/FLASH2_SS')
if ni is not None:
    B.Delete(ni)

# ---------------------------------------------------------------- VSYS on J3 pin 2
# J3 pin 2 is VSYS, the regulator input, so the board can run from 5 V on the header. USB VBUS
# reaches VSYS through the Schottky D2, so header power can't back-feed the USB port. Pi's VBUS
# pour is split in two: the USB side (J1 to D2's anode) and VSYS (D2's cathode, C1, U2's input).
# VSYS runs from D2 through U2's input pad and on to J3 under U2, between its pins and its tab,
# which leaves the 3V3 pour above it joined to U2's pin 2 and on to J3 pin 1.
d2 = place('D2', 104.0, 76.55, 180)
d2.Reference().SetPosition(P(103.0, 79.4))           # below the anode, clear of U2's pins
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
